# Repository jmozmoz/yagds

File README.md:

# yagds
This project is yet another garage door sensor.

Sensor data of changing door positions are captured by two reed sensors
connected to a ESP-01 module and
forwarded using the MQTT to a MQTT broker. A Python script subscribes to
these MQTT messages and implements a state machine representing the state of
the door (open, closed, moving). If the state of the door changes a Telegram
Bot notifies Telegram clients connected to it.

By using Telegram to distribute changes, the MQTT broker does not need to be
accessible from the internet. Also the Android Telegram Bot supports Android
Auto, so the garage door state can easily be sent to your car.

## Hardware

### ESP-01 module

The hardware is based on the ESP-01 module using the microchip
[ESP8266](https://en.wikipedia.org/wiki/ESP8266) microcontroller. This
microchip includes a micro controller with WIFI and TCP/IP capabilities and
can be programmed with the Arduino tool chain. The ESP-01 provides easy
access to 8 of the pins of the microchip of which up to 4 can be used as
general purpose input/output (GPIO): GPIO0, GPIO2, TX(GPIO1), RX(GPIO3)

But the voltage level of some of the GPIO pins are used to select the
[boot mode](https://github.com/esp8266/esp8266-wiki/wiki/Boot-Process#esp-boot-modes)
during power-up/after a reset. The configuration which finally worked for me,
is using GPIO0 and GPIO3 and make sure, that they are at high voltage
level (3.3 V) during reset.

### Carrier Board

The micro controller should go to deep sleep mode after the door reached the
open or closed position. This saves energy if the hardware should be powered
by battery. To wake-up it up again, changes at the reed contacts should
trigger a pulse on the RST pin. Based on the idea described
[here (in German)](http://esp8266-server.de/Reedkontakt.html) for both, GPIO0
and RX, a XOR gate is used to compare the signal with a delayed one. The latter
is produced by RC-circuits. If the signal changes, the delayed signal keeps is
different from the un-delayed signal and the XOR gate outputs one (the two
gates in the top left part of the schematics below). If at least one of
the signals has changed its state, the output of the OR gate is one.
The output of the OR gate is inverted by another XOR gate (top right of the
schematics) and used as input for the RST (reset) pin.

To make sure, that the GPIO pins are at high voltage to boot correctly the
output of the OR gate is delayed by another RC circuit and ORed with the
signals of the GPIO pins. So these pins stay at high until the boot-up
has been completed.

The RC circuits and the OR/XOR gates together with a voltage regulator
for the 3.3 V power supply of the gates and ESP-01 are combined on
a PCB board which carry the ESP-01.

The cables of the reed contacts are connected with RCA (cinch) connectors
to the carrier board. A micro USB socket is used for power supply.

The schematics and PCB layout can be found in folder [layout_kicad](layout_kicad/).
They were created using [KiCad](http://kicad-pcb.org/)

## Software

### ESP-01 Firmware
The [firmware of the ESP-01](uploadSensorData/) is developed using
[PlatformIO](https://platformio.org/).

The communication with the MQTT
broker and the handling of configuration data (including updating them
over the air/the MQTT broker) is handled by the library
[Homie](https://github.com/marvinroger/homie-esp8266).

The library [simpleTimer](https://github.com/jfturcot/SimpleTimer) is
used to timeout connection setup and putting the micro  controller into
deep sleep state.

LED debug output flashing patterns are generated using the library
[jled](https://github.com/jandelgado/jled).

To set the configuration, add the file `data/homie/config.json` and
upload it the ESP-01 using Upload SPIFFS image.
```
{
  "name": "YAGDS",
  "device_id": "door_sensor",
  "device_stats_interval": 60,
  "wifi": {
    "ssid": "xxx",
    "password": "yyy"
  },
  "mqtt": {
    "host": "alpha",
    "port": 8883,
    "base_topic": "homie/",
    "auth": true,
    "username": "aaa",
    "password": "bbb",
    "ssl": true,
    "ssl_fingerprint": "123456789abcedf"
  },
  "ota": {
    "enabled": false
  },
  "settings": {
    "sensor_update_interval": 2,
    "max_resend": 5,
    "connection_timeout": 30,
    "sleep_timeout": 10
  }
}
```

Known issues: 
* My board is affected by this 
[bug](https://github.com/marvinroger/homie-esp8266/issues/522), 
which requires 
[patching](https://github.com/esp8266/Arduino/issues/4061#issuecomment-368273656) 
the ESP8266 core for Arduino.
* To use SSL fingerprints for the connection between the ESP-01
and a MQTT broker, a special build flag has to set: 
`build_flags = -DASYNC_TCP_SSL_ENABLED=1`. Also consider this
[issue](https://github.com/marvinroger/async-mqtt-client/issues/53).

### Telegram Bot with state machine
A [Python script](mqtt_telegram_bot/) determines the state of
the door and sends out messages if the state changes.
[paho-mqtt](https://pypi.org/project/paho-mqtt/) is used
to subscribe to the MQTT broker to receive the message from the ESP-01.
The transitions between different states of the door are followed
using the library
[transitions](https://pypi.org/project/transitions/). Message
of the current signal of the reed contacts can trigger changes between
the different door states as shown in the picture below.

If a transition causes a state change, also message is sent using the
[Python Telegram Bot](https://pypi.org/project/python-telegram-bot/)
library.

The `bot.py` scripts looks for the configuration file 
`.mqtt_telegram_bot.ini` in the $HOME directory of the user, or
for the file specified with the option `-c` at startup. It 
contains information about the connection to the MQTT broker and the
Telegram Bot.
```
[MQTT]
broker = broker.address
ca = ~/mqtt_ca.crt
username = username
password = password
topics_path = homie/door_sensor/reeds/#

[Telegram]
token = TOKEN
chat_id = 12345
```

## Authors

* **Joachim Herb** - [jmozmoz](https://github.com/jmozmoz)

## License

This project is licensed under [GPL v3](LICENSE)

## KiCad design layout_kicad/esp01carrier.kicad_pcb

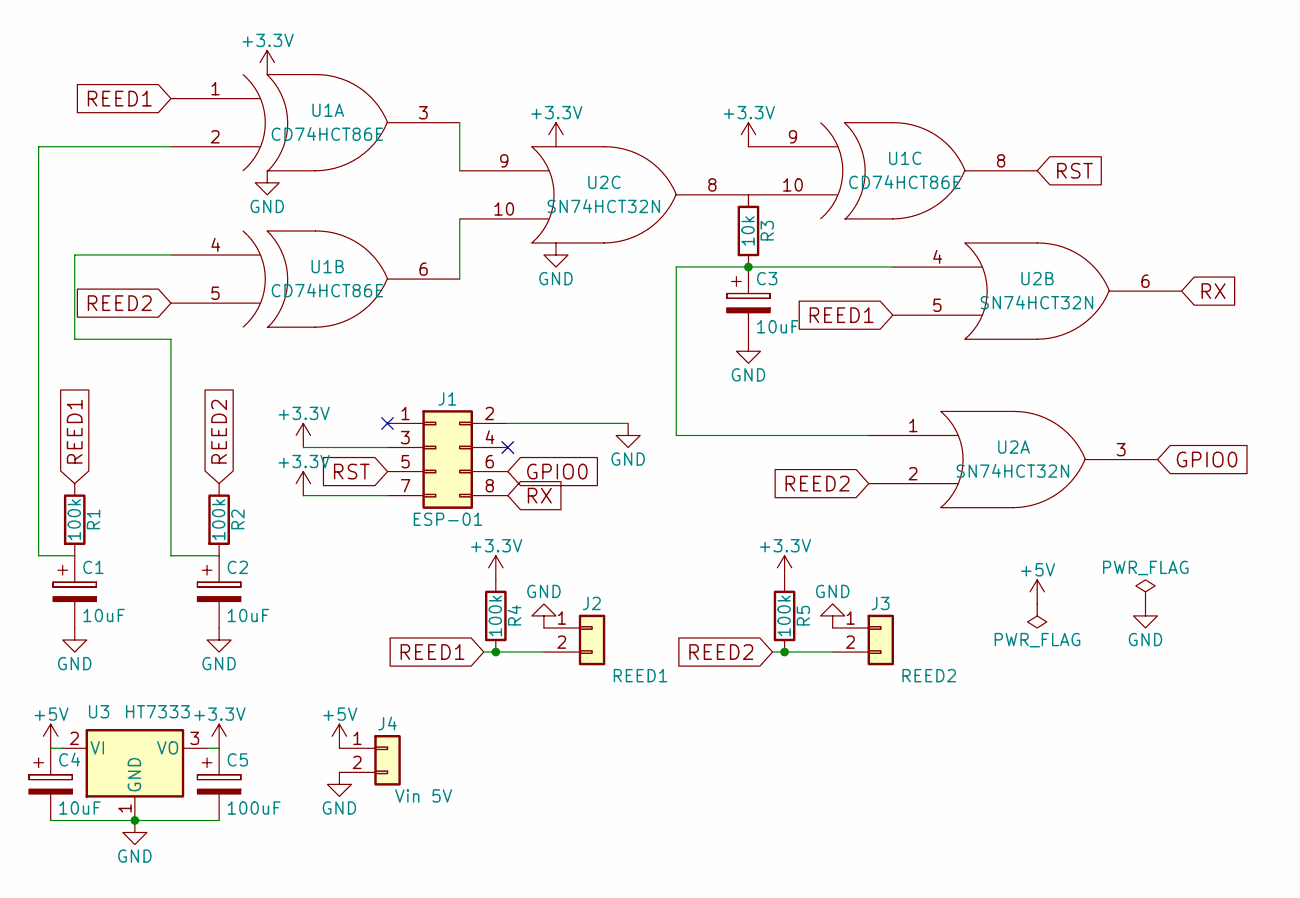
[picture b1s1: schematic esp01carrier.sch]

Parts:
C1, C2: 10uF; CP_Radial_D7.5mm_P2.50mm
C3: 10uF; CP_Radial_D6.3mm_P2.50mm
C4: 10uF; CP_Radial_D5.0mm_P2.50mm
C5: 100uF; CP_Radial_D6.3mm_P2.50mm
J1: ESP-01; Socket_Strip_Straight_2x04_Pitch2.54mm
J2: REED1; Pin_Header_Straight_1x02_Pitch2.54mm
J3: REED2; Pin_Header_Straight_1x02_Pitch2.54mm
J4: Vin 5V; Pin_Header_Straight_1x02_Pitch2.54mm
R1, R2, R4, R5: 100k; R_Axial_DIN0207_L6.3mm_D2.5mm_P7.62mm_Horizontal
R3: 10k; R_Axial_DIN0207_L6.3mm_D2.5mm_P7.62mm_Horizontal
U1: CD74HCT86E; DIP-14_W7.62mm
U2: SN74HCT32N; DIP-14_W7.62mm
U3: HT7333; TO-262_I2PAK_Vertical

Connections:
+3V3: C5.1, J1.3, J1.7, R4.1, R5.1, U1.9 (IN1), U1.14 (VCC), U2.14 (VCC), U3.3 (VO)
+5V: C4.1, J4.1, U3.2 (VI)
GND: C1.2, C2.2, C3.2, C4.2, C5.2, J1.2, J2.1, J3.1, J4.2, U1.7 (GND), U2.7 (GND), U3.1 (GND)
GPIO0: J1.6, U2.3
unnamed: C1.1, R1.2, U1.2 (IN2)
unnamed: C2.1, R2.2, U1.4 (IN1)
unnamed: C3.1, R3.2, U2.1, U2.4
unnamed: R3.1, U1.10 (IN2), U2.8
unnamed: U1.3 (OUT), U2.9
unnamed: U1.6 (OUT), U2.10
REED1: J2.2, R1.1, R4.2, U1.1 (IN1), U2.5
REED2: J3.2, R2.1, R5.2, U1.5 (IN2), U2.2
RST: J1.5, U1.8 (OUT)
RX: J1.8, U2.6

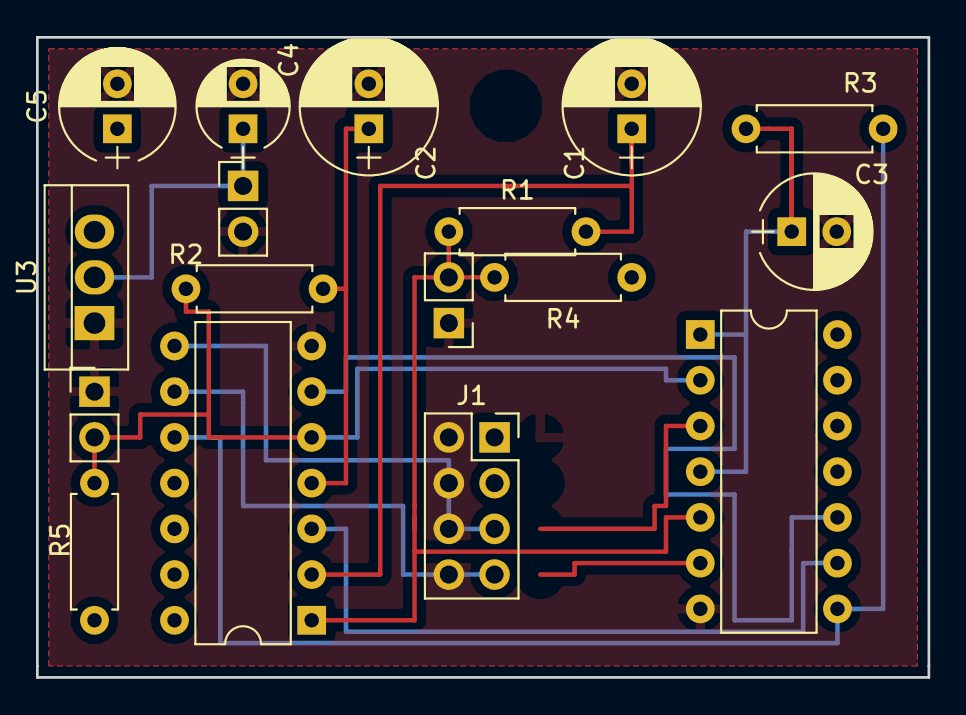
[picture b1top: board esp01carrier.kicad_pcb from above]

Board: 2 copper layers, 49.5 x 35.6 mm, 17 parts (0 on the bottom side), 14 nets.

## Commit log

2018-04-26 Initial commit
    Working example of bot forwarding messages from MQTT to Telegram
2018-04-26 gitignore
2018-05-06 Move bot to sub folder
2018-05-06 Add kicad project
2018-05-12 Add .gitignore
2018-05-14 First ESP01 firmware based on Homie using PlatformIO
2018-05-14 Improve sleep handling: Use timeout to force going to sleep
2018-05-16 use simpleTimer lib for all intervall/timeout handling
2018-05-16 Use non-development version of expressif8266
2018-05-16 Put timeout/interval settings in config.json
2018-05-23 Add LED state signaling (alternative to serial output)
2018-05-23 Change RC-curcuits to reduce current
2018-05-26 class for debug output (LED/serial), force maximal Wifi power
2018-05-27 Add eschema/ignore bak files
2018-06-10 Add username/password of MQTT broker. Move config handling to classes.
2018-06-11 Add topic to bot message
2018-06-13 Add state machine for garage door. Add tests for state machine
2018-06-13 .gitignore update
2018-06-13 Remove wrong import
2018-06-13 Another .gitignore
2018-06-14 Make number of times an open/closed status is resent configurable.
2018-06-14 Readme outline
2018-06-14 Fix wrong target state in transitions, add more tests.
    Update README.md with state machine graph.
2018-06-15 More README.md content
2018-06-15 Add config examples to README.md
2018-06-17 Telegram Bot chat_id has to be int
2018-07-04 Store last message and resend it at re-connect of user.
2022-08-22 Send reminder if door is not closed
2025-02-11 update for python3, send reminder messages
2025-02-12 reconnect to mqtt server to reset state
